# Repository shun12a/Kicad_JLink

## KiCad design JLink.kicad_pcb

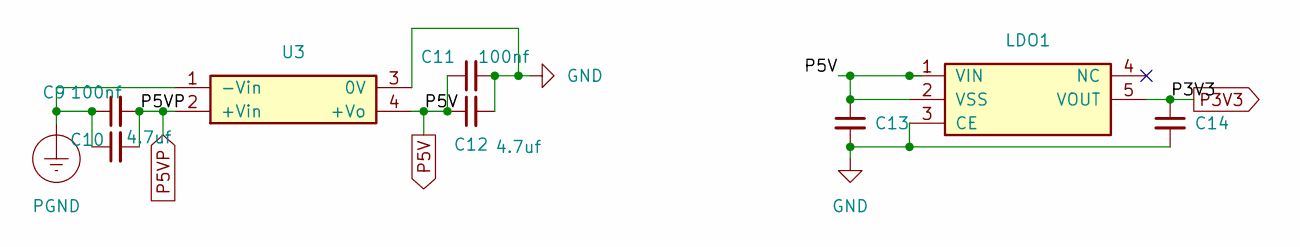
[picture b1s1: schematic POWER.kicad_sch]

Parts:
C9, C11: 100nf; 0603B104K101CT; Tolerance 10 %; Voltage Rating 100 V; Mpn 0603B104K101CT
C10, C12: 4.7uf; CC0603KRX5R8BB475; Tolerance 10 %; Voltage Rating 25 V; Mpn CC0603KRX5R8BB475
C13, C14: 0603B105K250NT; Tolerance 10 %; Voltage Rating 25 V; Mpn 0603B105K250NT
LDO1: ME6211C33M5G-N; Dropout Voltage 260 mV @200mA; Input Voltage 6 V; Mpn ME6211C33M5G-N
U3: B0505S-1W__Rlt; Input Voltage 4.5 V; Input Voltage (Max) 5.5 V; Mpn B0505S-1W__Rlt

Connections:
GND: C11.2, C12.2, C13.2, C14.2, LDO1.3 (CE), U3.3 (0V); also elsewhere on the board
P3V3: C14.1, LDO1.5 (VOUT); also elsewhere on the board
P5V: C11.1, C12.1, C13.1, LDO1.1 (VIN), LDO1.2 (VSS), U3.4 (+Vo); also elsewhere on the board
P5VP: C9.2, C10.2, U3.2 (+Vin); also elsewhere on the board
PGND: C9.1, C10.1, U3.1 (-Vin); also elsewhere on the board

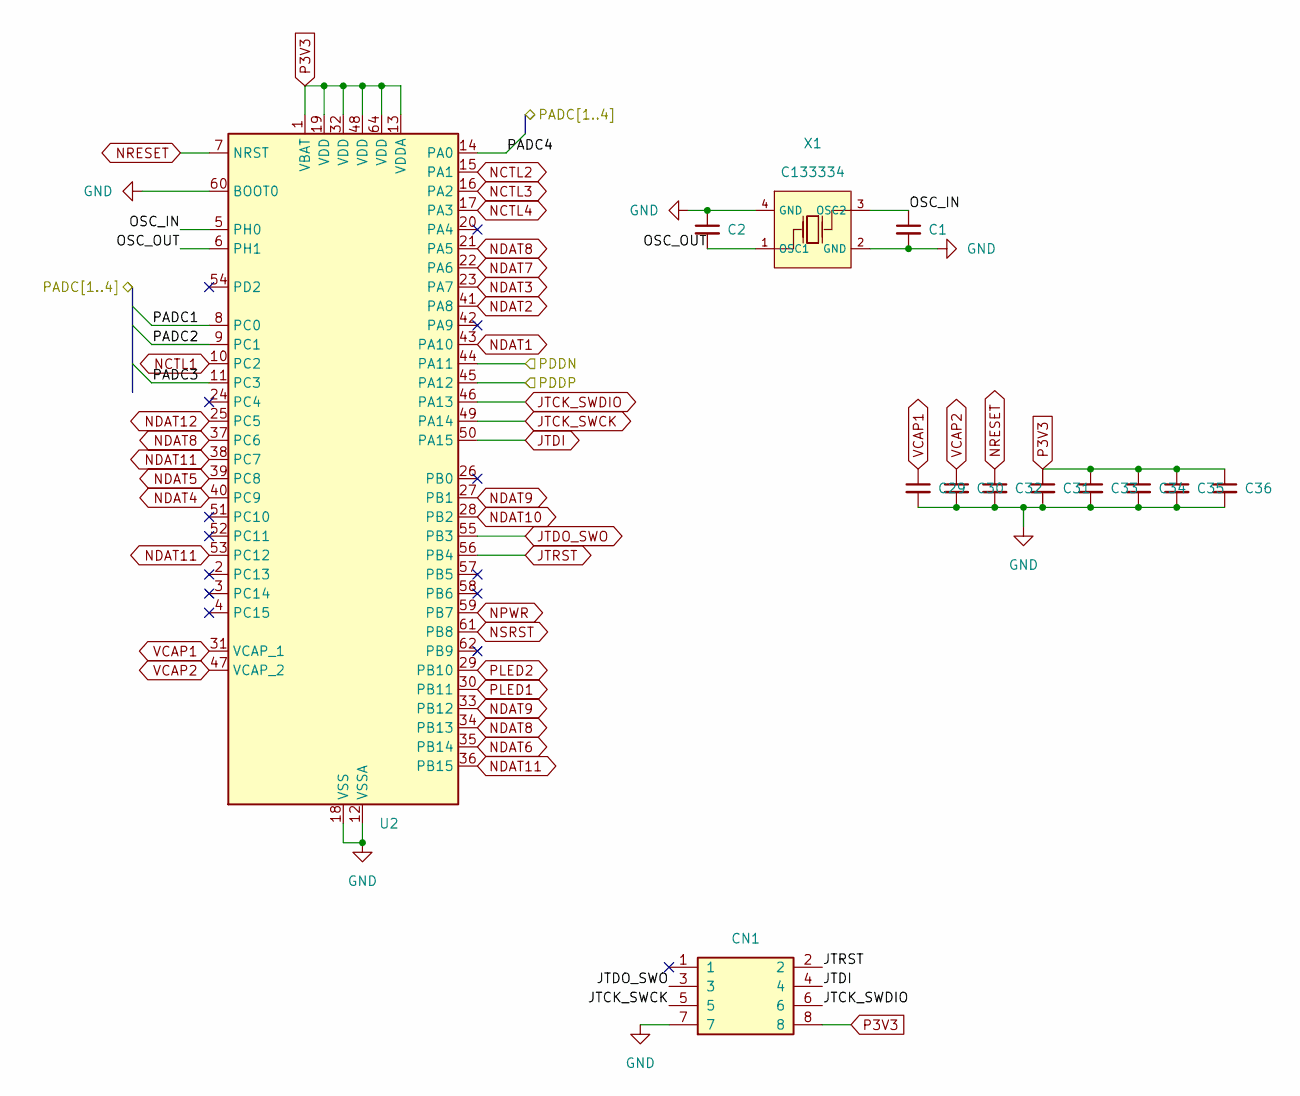
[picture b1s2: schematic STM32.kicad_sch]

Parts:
C1, C2: CL10C200JB81PNC; Tolerance 5 %; Voltage Rating 50 V; Mpn CL10C200JB81PNC
C29, C30, C31, C32, C33, C34, C35, C36: 0603B225K250NT; Tolerance 10 %; Voltage Rating 25 V; Mpn 0603B225K250NT
CN1: A2541WV-2x4P; Mpn A2541WV-2x4P
U2: STM32F205RET6; Supply Voltage 3.6 V; Mpn STM32F205RET6
X1: CRYSTAL-SMD_4P-L3.2-W2.5-BL; LCSC Part C133334

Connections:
/ADC1: U2.8 (PC0); also elsewhere on the board
/ADC2: U2.9 (PC1); also elsewhere on the board
/ADC3: U2.11 (PC3); also elsewhere on the board
/ADC4: U2.14 (PA0); also elsewhere on the board
/PDDN: U2.44 (PA11); also elsewhere on the board
/PDDP: U2.45 (PA12); also elsewhere on the board
/STM32/OSC_IN: C1.1, U2.5 (PH0), X1.3 (OSC2)
/STM32/OSC_OUT: C2.2, U2.6 (PH1), X1.1 (OSC1)
GND: C1.2, C2.1, C29.2, C30.2, C31.2, C32.2, C33.2, C34.2, C35.2, C36.2, CN1.7, U2.12 (VSSA), U2.18 (VSS), U2.60 (BOOT0), U2.63 (VSS), X1.2 (GND), X1.4 (GND); also elsewhere on the board
JTCK_SWCK: CN1.5, U2.49 (PA14)
JTCK_SWDIO: CN1.6, U2.46 (PA13)
JTDI: CN1.4, U2.50 (PA15)
JTDO_SWO: CN1.3, U2.55 (PB3)
JTRST: CN1.2, U2.56 (PB4)
NCTL1: U2.10 (PC2); also elsewhere on the board
NCTL2: U2.15 (PA1); also elsewhere on the board
NCTL3: U2.16 (PA2); also elsewhere on the board
NCTL4: U2.17 (PA3); also elsewhere on the board
NDAT1: U2.43 (PA10); also elsewhere on the board
NDAT2: U2.41 (PA8); also elsewhere on the board
NDAT3: U2.23 (PA7); also elsewhere on the board
NDAT4: U2.40 (PC9); also elsewhere on the board
NDAT5: U2.39 (PC8); also elsewhere on the board
NDAT6: U2.35 (PB14); also elsewhere on the board
NDAT7: U2.22 (PA6); also elsewhere on the board
NDAT8: U2.21 (PA5), U2.34 (PB13), U2.37 (PC6); also elsewhere on the board
NDAT9: U2.27 (PB1), U2.33 (PB12); also elsewhere on the board
NDAT10: U2.28 (PB2); also elsewhere on the board
NDAT11: U2.36 (PB15), U2.38 (PC7), U2.53 (PC12); also elsewhere on the board
NDAT12: U2.25 (PC5); also elsewhere on the board
NPWR: U2.59 (PB7); also elsewhere on the board
NRESET: C32.1, U2.7 (NRST)
NSRST: U2.61 (PB8); also elsewhere on the board
P3V3: C31.1, C33.1, C34.1, C35.1, C36.1, CN1.8, U2.1 (VBAT), U2.13 (VDDA), U2.19 (VDD), U2.32 (VDD), U2.48 (VDD), U2.64 (VDD); also elsewhere on the board
PLED1: U2.30 (PB11); also elsewhere on the board
PLED2: U2.29 (PB10); also elsewhere on the board
VCAP1: C29.1, U2.31 (VCAP_1)
VCAP2: C30.1, U2.47 (VCAP_2)

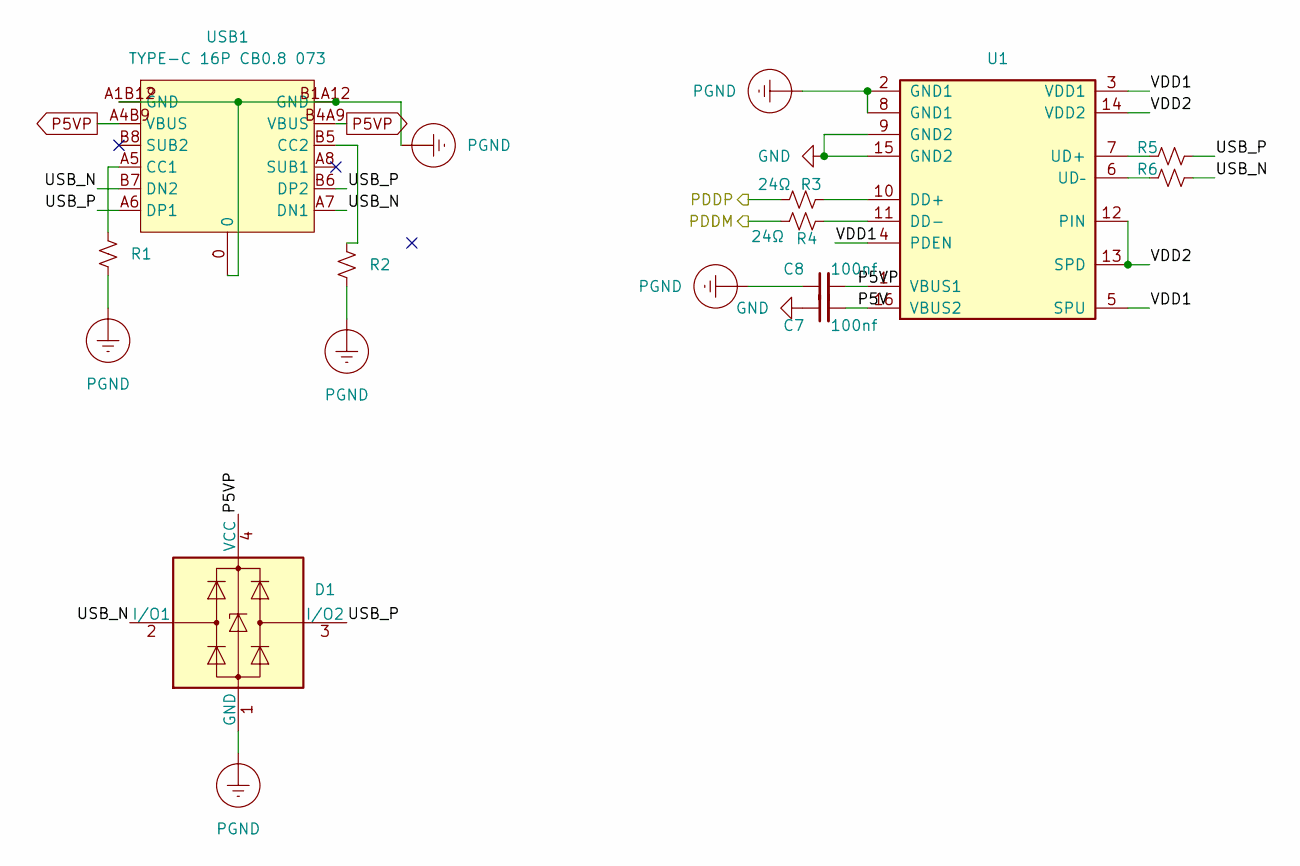
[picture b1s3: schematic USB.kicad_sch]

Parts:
C7, C8: 100nf; 0603B104K101CT; Tolerance 10 %; Voltage Rating 100 V; Mpn 0603B104K101CT
D1: PRTR5V0U2X__NXP Semiconductors; Breakdown Voltage 9 V; Clamping Voltage 7.5 V; Mpn PRTR5V0U2X__NXP Semiconductors
R1, R2: RTT03512JTP; Power Rating 100 mW; Tolerance 5 %; Mpn RTT03512JTP
R3, R4: 24Ω; RC0603FR-0724RL; Power Rating 100 mW; Tolerance 1 %; Mpn RC0603FR-0724RL
R5, R6: RC0603FR-0724RL; Power Rating 100 mW; Tolerance 1 %; Mpn RC0603FR-0724RL
U1: ADUM3160BRWZ-RL; Supply Voltage 5.5 V; Mpn ADUM3160BRWZ-RL
USB1: TYPE-C 16P CB0.8 073; USB-C-SMD_TYPE-C-16P-CB0.8-073; LCSC Part C2906289

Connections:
/PDDN: R4.1; also elsewhere on the board
/PDDP: R3.1; also elsewhere on the board
/USB/DD+: R3.2, U1.10 (DD+)
/USB/DD-: R4.2, U1.11 (DD-)
/USB/UD+: R5.1, U1.7 (UD+)
/USB/UD-: R6.1, U1.6 (UD–)
/USB/USB_N: D1.2 (I/O1), R6.2, USB1.A7 (DN1), USB1.B7 (DN2)
/USB/USB_P: D1.3 (I/O2), R5.2, USB1.A6 (DP1), USB1.B6 (DP2)
/USB/VDD1: U1.3 (VDD1), U1.4 (PDEN), U1.5 (SPU); also elsewhere on the board
/USB/VDD2: U1.12 (PIN), U1.13 (SPD), U1.14 (VDD2); also elsewhere on the board
GND: C7.1, U1.9 (GND2), U1.15 (GND2); also elsewhere on the board
unnamed: R1.1, USB1.A5 (CC1)
unnamed: R2.1, USB1.B5 (CC2)
P5V: C7.2, U1.16 (VBUS2); also elsewhere on the board
P5VP: C8.2, D1.4 (VCC), U1.1 (VBUS1), USB1.A4B9 (VBUS), USB1.B4A9 (VBUS); also elsewhere on the board
PGND: C8.1, D1.1 (GND), R1.2, R2.2, U1.2 (GND1), U1.8 (GND1), USB1.0, USB1.A1B12 (GND), USB1.B1A12 (GND); also elsewhere on the board

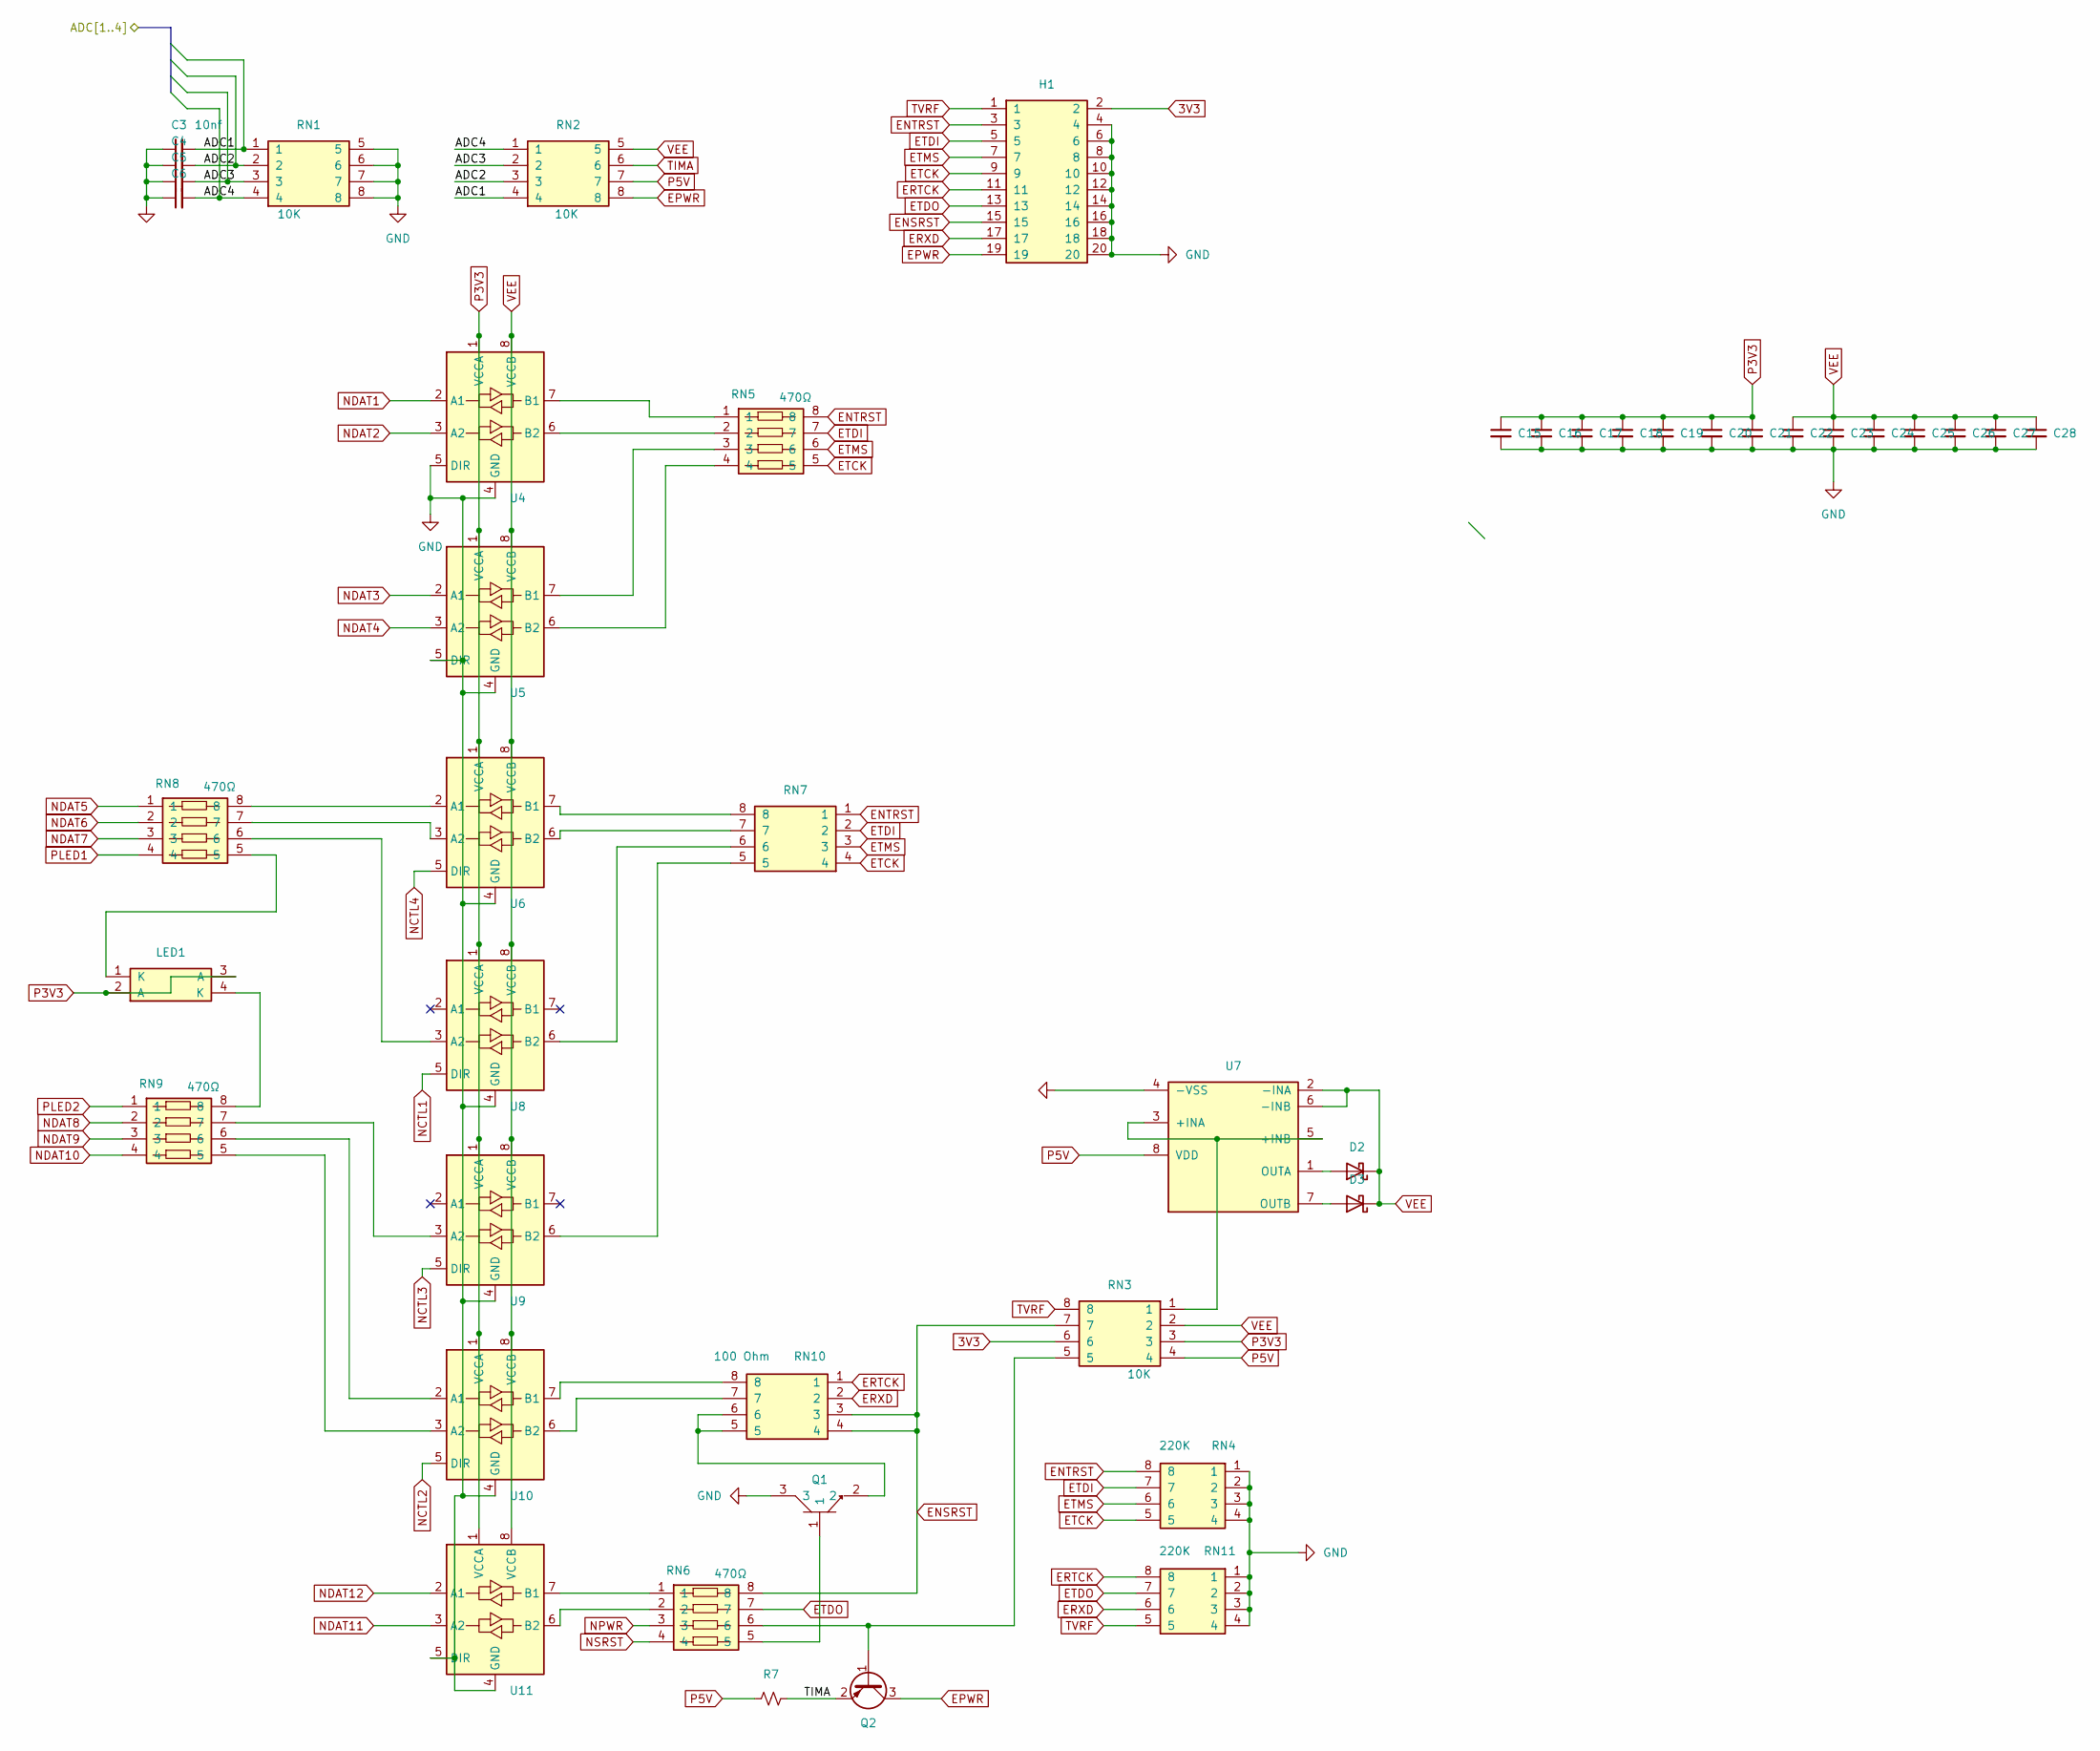
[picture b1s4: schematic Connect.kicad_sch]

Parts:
C3: 10nf; CC0603KRX7R6BB103; Tolerance 10 %; Voltage Rating 10 V; Mpn CC0603KRX7R6BB103
C4, C5, C6: CC0603KRX7R6BB103; Tolerance 10 %; Voltage Rating 10 V; Mpn CC0603KRX7R6BB103
C15, C16, C17, C18, C19, C20, C21, C22, C23, C24, C25, C26, C27, C28: CL10B104KC8NNNC; Tolerance 10 %; Voltage Rating 100 V; Mpn CL10B104KC8NNNC
D2, D3: MBR0530__YANGJIE; Mpn MBR0530__YANGJIE
H1: PZ200-2-10-Z; Current Rating 1.5 A; Mpn PZ200-2-10-Z
LED1: SZYY0603RB2; Forward Voltage 2.2 V; Power Rating 40 mW; Mpn SZYY0603RB2
Q1: SS8050__SHIKUES; Mpn SS8050__SHIKUES
Q2: SS8550 Y2; Mpn SS8550 Y2
R7: RK73Z1JTTD; Power Rating 1 W; Tolerance 1 %; Mpn RK73Z1JTTD
RN1, RN2, RN3: 10K; 4D03WGJ0472T5E; Power Rating 62.5 mW; Tolerance 5 %; Mpn 4D03WGJ0472T5E
RN4, RN11: 220K; 4D03WGJ0224T5E; Power Rating 62.5 mW; Tolerance 5 %; Mpn 4D03WGJ0224T5E
RN5, RN6, RN8, RN9: 470Ω; 4D03WGJ0471T5E; Power Rating 62.5 mW; Tolerance 5 %; Mpn 4D03WGJ0471T5E
RN7: YC164-FR-07100RL; Power Rating 62.5 mW; Tolerance 1 %; Mpn YC164-FR-07100RL
RN10: 100 Ohm; YC164-FR-07100RL; Power Rating 62.5 mW; Tolerance 1 %; Mpn YC164-FR-07100RL
U4, U5, U6, U8, U9, U10, U11: SN74LVC2T45DCUR; Supply Voltage 5.5 V; Mpn SN74LVC2T45DCUR
U7: MCP6002T-I_SN; Supply Voltage 1.8 V; Supply Voltage (Max) 6 V; Mpn MCP6002T-I/SN

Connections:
3V3: H1.2, RN3.6
/ADC1: C3.2, RN1.1, RN2.4; also elsewhere on the board
/ADC2: C4.2, RN1.2, RN2.3; also elsewhere on the board
/ADC3: C5.2, RN1.3, RN2.2; also elsewhere on the board
/ADC4: C6.2, RN1.4, RN2.1; also elsewhere on the board
ENSRST: H1.15, RN3.7, RN6.8, RN10.3, RN10.4
ENTRST: H1.3, RN4.8, RN5.8, RN7.1
EPWR: H1.19, Q2.3 (C), RN2.8
ERTCK: H1.11, RN10.1, RN11.8
ERXD: H1.17, RN10.2, RN11.6
ETCK: H1.9, RN4.5, RN5.5, RN7.4
ETDI: H1.5, RN4.7, RN5.7, RN7.2
ETDO: H1.13, RN6.7, RN11.7
ETMS: H1.7, RN4.6, RN5.6, RN7.3
GND: C3.1, C4.1, C5.1, C6.1, C15.2, C16.2, C17.2, C18.2, C19.2, C20.2, C21.2, C22.2, C23.2, C24.2, C25.2, C26.2, C27.2, C28.2, H1.4, H1.6, H1.8, H1.10, H1.12, H1.14, H1.16, H1.18, H1.20, Q1.3, RN1.5, RN1.6, RN1.7, RN1.8, RN4.1, RN4.2, RN4.3, RN4.4, RN11.1, RN11.2, RN11.3, RN11.4, U4.4 (GND), U4.5 (DIR), U5.4 (GND), U5.5 (DIR), U6.4 (GND), U7.4 (-VSS), U8.4 (GND), U9.4 (GND), U10.4 (GND), U11.4 (GND), U11.5 (DIR); also elsewhere on the board
NCTL1: U8.5 (DIR); also elsewhere on the board
NCTL2: U10.5 (DIR); also elsewhere on the board
NCTL3: U9.5 (DIR); also elsewhere on the board
NCTL4: U6.5 (DIR); also elsewhere on the board
NDAT1: U4.2 (A1); also elsewhere on the board
NDAT2: U4.3 (A2); also elsewhere on the board
NDAT3: U5.2 (A1); also elsewhere on the board
NDAT4: U5.3 (A2); also elsewhere on the board
NDAT5: RN8.1; also elsewhere on the board
NDAT6: RN8.2; also elsewhere on the board
NDAT7: RN8.3; also elsewhere on the board
NDAT8: RN9.2; also elsewhere on the board
NDAT9: RN9.3; also elsewhere on the board
NDAT10: RN9.4; also elsewhere on the board
NDAT11: U11.3 (A2); also elsewhere on the board
NDAT12: U11.2 (A1); also elsewhere on the board
NPWR: RN6.3; also elsewhere on the board
NSRST: RN6.4; also elsewhere on the board
unnamed: D2.2 (A), U7.1 (OUTA)
unnamed: D3.2 (A), U7.7 (OUTB)
unnamed: LED1.1 (K), RN8.5
unnamed: LED1.4 (K), RN9.8
unnamed: Q1.1, RN6.5
unnamed: Q1.2, RN10.5, RN10.6
unnamed: Q2.1 (B), RN3.5, RN6.6
unnamed: RN5.1, U4.7 (B1)
unnamed: RN5.2, U4.6 (B2)
unnamed: RN5.3, U5.7 (B1)
unnamed: RN5.4, U5.6 (B2)
unnamed: RN8.8, U6.2 (A1)
unnamed: RN8.7, U6.3 (A2)
unnamed: RN7.8, U6.7 (B1)
unnamed: RN7.7, U6.6 (B2)
unnamed: RN3.1, U7.3 (+INA), U7.5 (+INB)
unnamed: RN8.6, U8.3 (A2)
unnamed: RN7.6, U8.6 (B2)
unnamed: RN9.7, U9.3 (A2)
unnamed: RN7.5, U9.6 (B2)
unnamed: RN9.6, U10.2 (A1)
unnamed: RN9.5, U10.3 (A2)
unnamed: RN10.8, U10.7 (B1)
unnamed: RN10.7, U10.6 (B2)
unnamed: RN6.1, U11.7 (B1)
unnamed: RN6.2, U11.6 (B2)
P3V3: C15.1, C16.1, C17.1, C18.1, C19.1, C20.1, C21.1, LED1.2 (A), LED1.3 (A), RN3.3, U4.1 (VCCA), U5.1 (VCCA), U6.1 (VCCA), U8.1 (VCCA), U9.1 (VCCA), U10.1 (VCCA), U11.1 (VCCA); also elsewhere on the board
P5V: R7.1, RN2.7, RN3.4, U7.8 (VDD); also elsewhere on the board
PLED1: RN8.4; also elsewhere on the board
PLED2: RN9.1; also elsewhere on the board
TIMA: Q2.2 (E), R7.2, RN2.6
TVRF: H1.1, RN3.8, RN11.5
VEE: C22.1, C23.1, C24.1, C25.1, C26.1, C27.1, C28.1, D2.1 (K), D3.1 (K), RN2.5, RN3.2, U4.8 (VCCB), U5.8 (VCCB), U6.8 (VCCB), U7.2 (-INA), U7.6 (-INB), U8.8 (VCCB), U9.8 (VCCB), U10.8 (VCCB), U11.8 (VCCB)

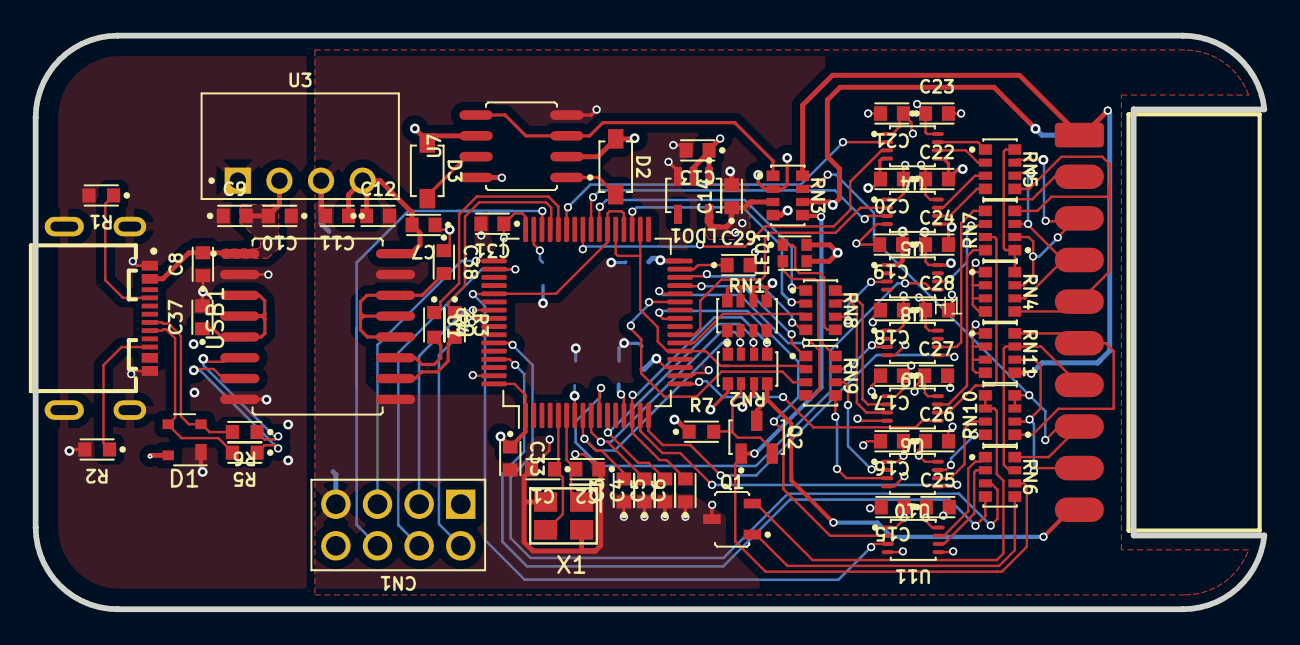
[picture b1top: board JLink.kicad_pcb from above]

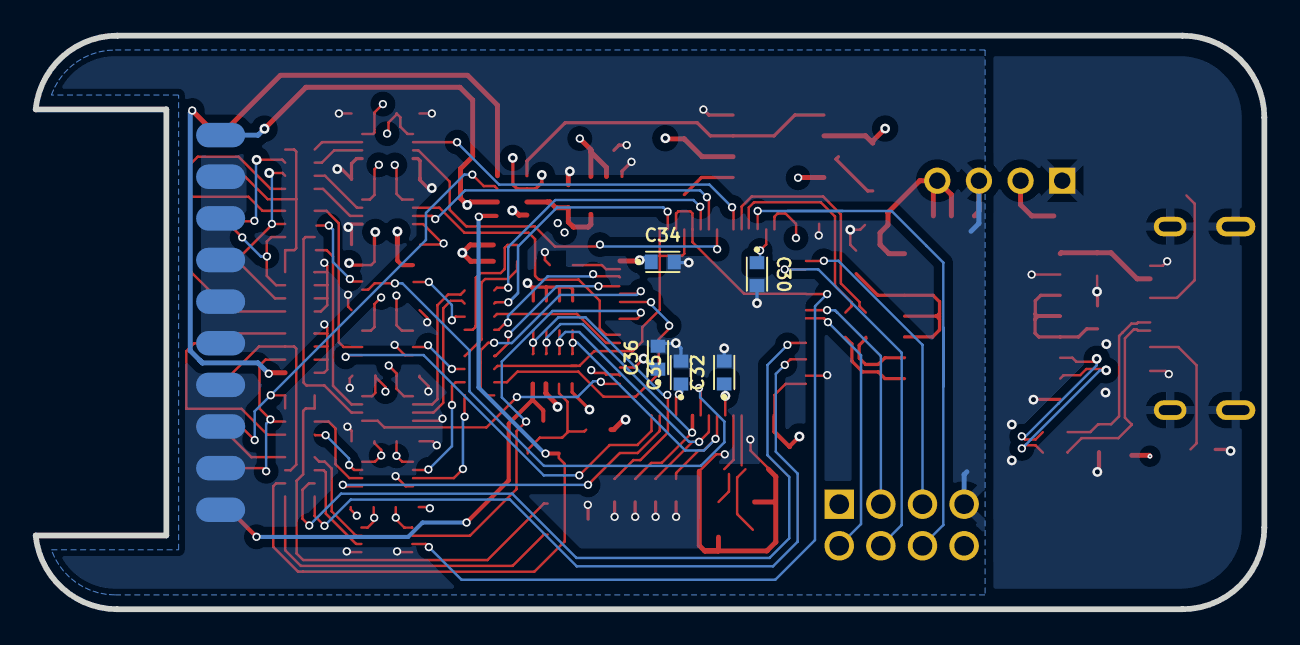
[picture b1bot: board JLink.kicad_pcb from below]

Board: 4 copper layers, 75.0 x 35.0 mm, 78 parts (5 on the bottom side), 90 nets.

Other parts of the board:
C37, C38: 100nf; 0603B104K101CT

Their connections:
/USB/VDD1: C37.1; also elsewhere on the board
/USB/VDD2: C38.2; also elsewhere on the board
GND: C38.1; also elsewhere on the board
PGND: C37.2; also elsewhere on the board

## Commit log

2025-06-26 2025/6/26
2025-06-27 2025/6/27：添加Lib ODBC库元器件
2025-06-27 取消提交backup文件
2025-06-29 20250630
2025-07-01 基本完成
2025-07-09 修改内容中
2025-07-14 JLINK will complite
2025-07-25 2025/07/25
2025-07-28 修改提交的文件选择
2025-07-30 合并远程更新并解决冲突
2025-08-03 添加覆铜GND和PGND
2025-08-07 20250807基本完成，只剩下检查
2025-08-07 20250807修改优化部分孤岛
